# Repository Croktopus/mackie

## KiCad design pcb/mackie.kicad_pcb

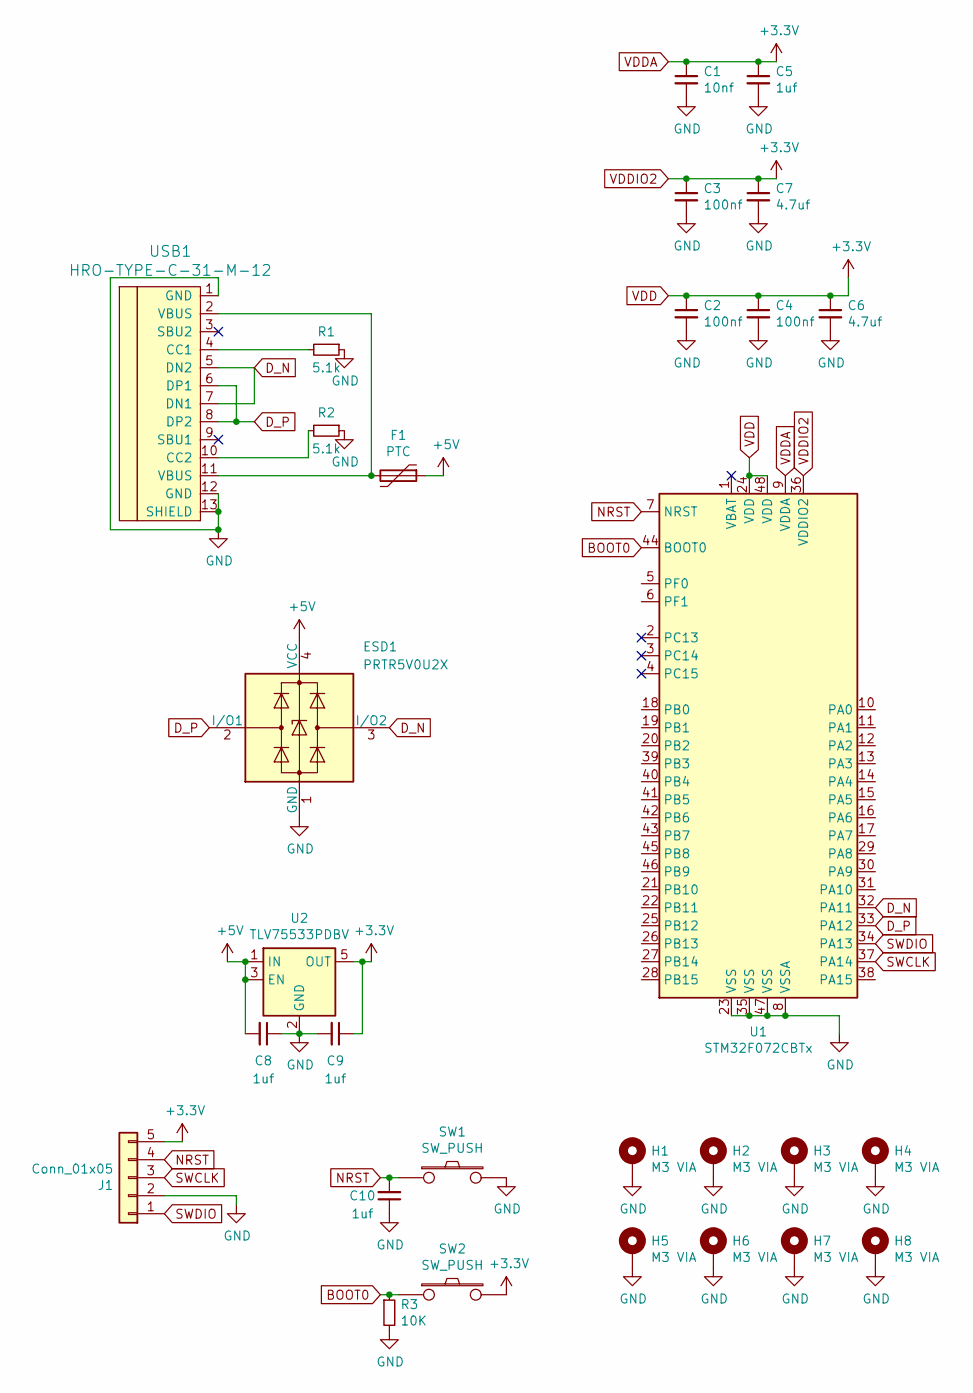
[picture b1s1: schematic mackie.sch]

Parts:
C1: 10nf; C_0603_1608Metric
C2, C3, C4: 100nf; C_0603_1608Metric
C5, C8, C9, C10: 1uf; C_0603_1608Metric
C6, C7: 4.7uf; C_0603_1608Metric
ESD1: PRTR5V0U2X; SOT-143
F1: PTC; Fuse_0805_2012Metric
H1, H2, H3, H4, H5, H6, H7, H8: M3 VIA; MountingHole_3.2mm_M3_Pad_Via
J1: Conn_01x05; PinSocket_1x05_P2.00mm_Vertical
R1, R2: 5.1k; R_0603_1608Metric
R3: 10K; R_0603_1608Metric
SW1, SW2: SW_PUSH; SW_SPST_SKQG_WithStem
U1: STM32F072CBTx; LQFP-48_7x7mm_P0.5mm
U2: TLV75533PDBV; SOT-23-5
USB1: HRO-TYPE-C-31-M-12; HRO-TYPE-C-31-M-12-Assembly

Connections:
+5V: C8.2, ESD1.4 (VCC), F1.1, U2.1 (IN), U2.3 (EN)
BOOT0: R3.1, SW2.1, U1.44 (BOOT0)
D_N: ESD1.3 (I/O2), U1.32 (PA11), USB1.5 (DN2), USB1.7 (DN1)
D_P: ESD1.2 (I/O1), U1.33 (PA12), USB1.6 (DP1), USB1.8 (DP2)
GND: C1.2, C2.2, C3.2, C4.2, C5.2, C6.2, C7.2, C8.1, C9.2, C10.1, ESD1.1 (GND), H1.1, H2.1, H3.1, H4.1, H5.1, H6.1, H7.1, H8.1, J1.2, R1.1, R2.1, R3.2, SW1.2, U1.8 (VSSA), U1.23 (VSS), U1.35 (VSS), U1.47 (VSS), U2.2 (GND), USB1.1 (GND), USB1.12 (GND), USB1.13 (SHIELD)
NRST: C10.2, J1.4, SW1.1, U1.7 (NRST)
unnamed: F1.2, USB1.2 (VBUS), USB1.11 (VBUS)
unnamed: R1.2, USB1.4 (CC1)
unnamed: R2.2, USB1.10 (CC2)
SWCLK: J1.3, U1.37 (PA14)
SWDIO: J1.1, U1.34 (PA13)
VDD: C1.1, C2.1, C3.1, C4.1, C5.1, C6.1, C7.1, C9.1, J1.5, SW2.2, U1.9 (VDDA), U1.24 (VDD), U1.36 (VDDIO2), U1.48 (VDD), U2.5 (OUT)

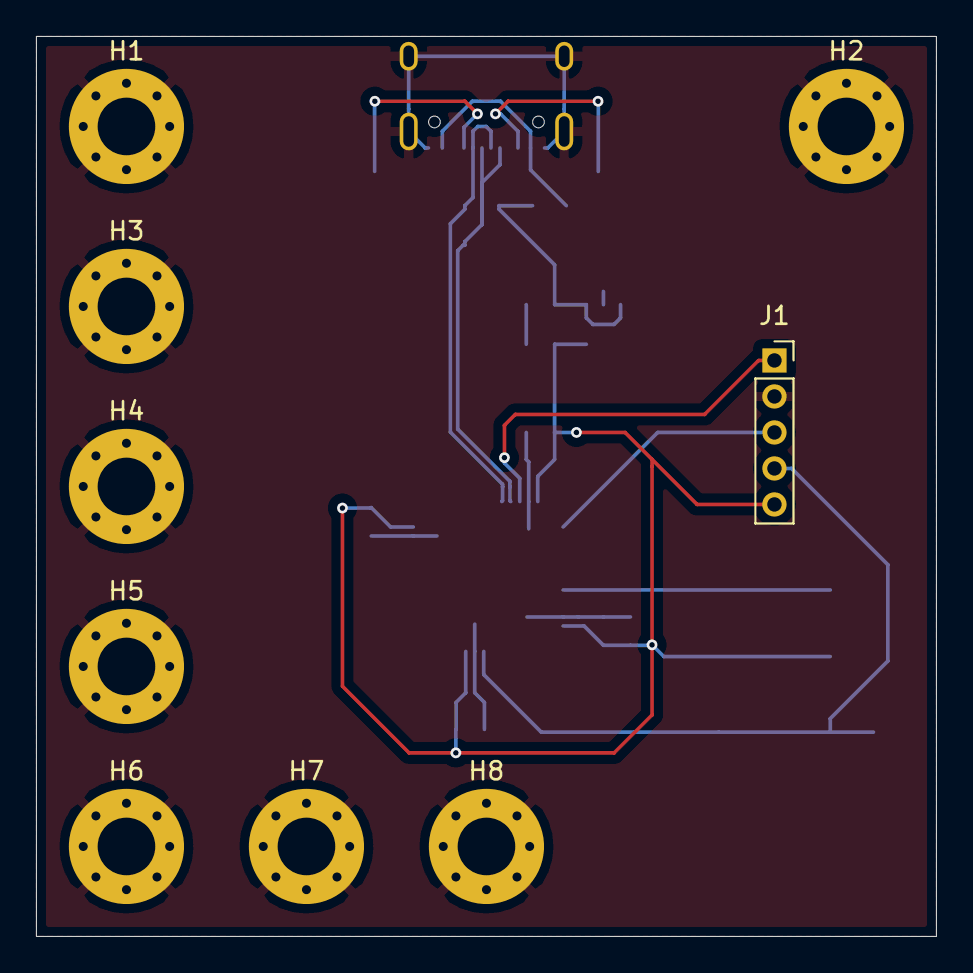
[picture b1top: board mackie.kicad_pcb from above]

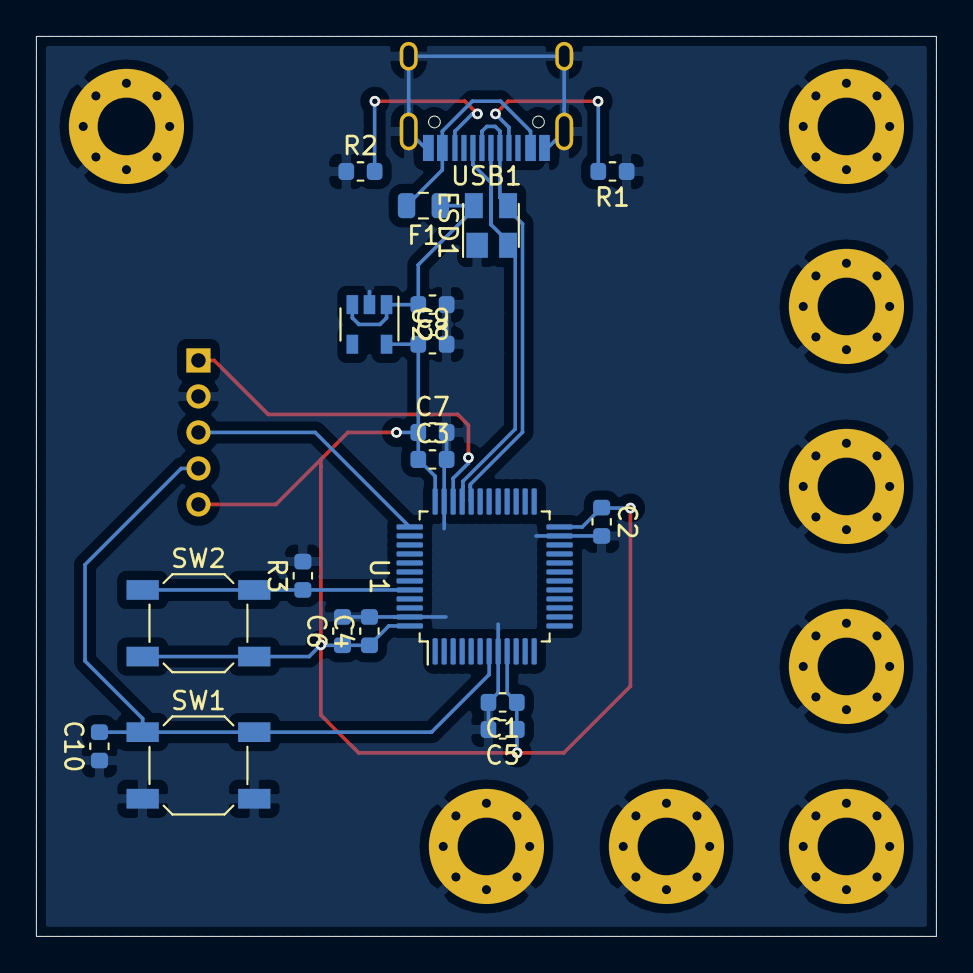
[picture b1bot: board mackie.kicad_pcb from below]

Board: 2 copper layers, 50.0 x 50.0 mm, 29 parts (20 on the bottom side), 12 nets.

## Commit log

2019-07-07 initial
2019-07-07 added debouncing cap
2019-07-30 fucking with a switch matrix
